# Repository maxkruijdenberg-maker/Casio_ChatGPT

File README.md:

# ChatGPT voor Casio — V40.1

Rustigere interface, modelinfo op F2 en een volledige verbindingscontrole. Na iedere bevestigde modelkeuze volgt automatisch één kleine betaalde API-test. Het actieve model wordt alleen bevestigd met passende API-modelmetadata.

[V40.1 downloaden](https://github.com/maxkruijdenberg-maker/Casio_ChatGPT/archive/refs/tags/download-v40.1-r1.zip) · [Handleiding](docs/V40.1-HANDLEIDING.md) · [Bijwerken](UPGRADE-V40.1.md) · [Alle downloads](DOWNLOADS.md)

Werk de Casio-app én je wifi-module bij. Er zijn aparte builds voor de ATOM-testbench en de ESP32-C6 Rev E-print. Behoud CGPT3; volledig wissen is niet nodig. Internet/account/modelcontrole gebruikt een echte kleine aanvraag en geeft geen exact tegoedsaldo. Zie de handleiding voor kosten en annuleren.

De builds en hosttests slagen; echte hardware/API-tests voor deze nieuwe versie moet je nog uitvoeren. De bestaande Rev E-productiebestanden blijven beschikbaar. Voor de nieuwe zelf te solderen XIAO-print gebruik je de aparte Rev G-bestanden hieronder.

## Actuele PCB: Rev G, drie Casio-draden

**Voor alleen Casio TX/RX/GND: gebruik Rev G. Rev F vereist een vierde VIO-draad en is daarvoor niet geschikt.**

[Download JLCPCB-set](https://github.com/maxkruijdenberg-maker/Casio_ChatGPT/archive/refs/tags/download-pcb-revg-r1.zip) · [Drie productie-bestanden](hardware/RevG-XIAO-3wire-06mm-OSP) · [Onderdeelcontrole](hardware/RevG-XIAO-ontwerp/ONDERDELENCONTROLE.md) · [Nieuwe XIAO-firmware + Casio-app](https://github.com/maxkruijdenberg-maker/Casio_ChatGPT/archive/refs/tags/download-xiao-revg-r1.zip)

Rev G: eigen XIAO zonder headerrails; 38 fabriekscomponenten / 20 codes; 89×34mm, 0,6mm, 2 lagen, OSP. Driepolige JST GH-uitgang; geen VIO-draad. TI-voedingsland/mask/stencil-patroon verwerkt; nieuwe uitgang met normale 3V3 UART-polariteit. Alleen de bijbehorende Rev G-firmware gebruiken. 26 hosttestgroepen en XIAO-build slagen; digitale controles schoon. Eerste PCBA nog fysiek te testen. [Handleiding en schema](hardware/RevG-XIAO-ontwerp/README.md).

## Installeren en bouwen

Open START-HIER.html uit het uitgepakte klantpakket. Arduino IDE 2, ESP32-core 3.3.0 en ArduinoJson 7.4.2 zijn gebruikt. De ATOM-sketch staat in atom/ChatGPTAtom, de C6-sketch in esp32c6/ChatGPTC6. Voor C6: ESP32C6 Dev Module, 4 MB, Huge APP, USB CDC uit. Laat alle headers bij de sketches staan.

ASAN_OPTIONS=detect_leaks=0 bash tools/test.sh draait de hosttests in de voorbereide omgeving. tools/sync_c6.py synchroniseert de gedeelde backend met behoud van de aparte C6-pinnen en zendsper.

[Schermvoorbeelden](docs/design/V40.1-actual-screens.png) · [Validatiestatus](docs/V40.1-CONTROLE-VOOR-VERKOOP.md) · [PCB-bestanden Rev E 0,6 mm/OSP](hardware/RevE-06mm-OSP)

Oudere versies blijven beschikbaar via de Git-tags en bestaande upgradegidsen.

V40.1: Info op F2; Model toont de bevestigde naam. De statusbadge verschijnt alleen op het chatbeginscherm. Eindtekens en onzichtbare opmaak worden beter weergegeven. Na 35 seconden zonder Casio-contact schakelt de wifi-radio uit en gaat de CPU naar 80 MHz; UART-contact herstelt de normale werking. Deze stroom- en herverbindingswerking is nog niet fysiek gemeten.

## Oudere PCB: Rev F, met vierde Casio-VIO-aansluiting

[Download JLCPCB-pakket](https://github.com/maxkruijdenberg-maker/Casio_ChatGPT/archive/refs/tags/download-pcb-revf-r1.zip) · [Alleen drie productie-bestanden](hardware/RevF-XIAO-06mm-OSP) · [Ontwerp, maatvoering en controles](hardware/RevF-XIAO-ontwerp/README.md) · [Download XIAO-firmware + Casio-app](xiao/ChatGPT-XIAO-RevF-installatie.zip)

89 × 34 mm L-vorm, 0,6 mm, 2 lagen, OSP. JLCPCB monteert 41 SMT-onderdelen; U5 blijft leeg voor jouw eigen Seeed XIAO ESP32-C6. Veertien soldeergaten, geen headerrails, USB-C binnen de getekende contour, J3/J4 aan het rechteruiteinde. Geen schakelaar: programmeer de XIAO eerst los. Voor eventueel later USB-onderhoud altijd J3 los vóór USB; USB los vóór J3 terugplaatsen.

Gebruik uitsluitend de **XIAO**-firmware voor Rev F: RX GPIO17, TX GPIO16. De Atom- en Rev E-builds hebben andere pinnen. [Arduino IDE-instellingen](xiao/README.md).

Digitale controles: DRC/ERC/parity schoon; boorgaten, Gerber-padcentra en BOM/CPL gecontroleerd; XIAO-build geslaagd. De echte 7mm-inbouwhoogte, voeding/wifi-pieken, RF en UART moeten op een eerste PCBA worden getest. Dit is nog geen fysiek gekwalificeerde verkoopserie.

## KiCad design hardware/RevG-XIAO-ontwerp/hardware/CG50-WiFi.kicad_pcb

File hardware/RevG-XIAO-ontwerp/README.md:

# Rev G — XIAO ESP32-C6, alleen TX / RX / GND

**Gebruik deze versie voor de drie-draads Casio-aansluiting. Rev F vereiste een vierde VIO-draad en past niet bij die wens. Meng geen Rev F-hardware of firmware met Rev G.**

[Onderdeelcontrole en ontwerpkeuzes](ONDERDELENCONTROLE.md)

De XIAO wordt door jou vóór montage los geprogrammeerd en daarna op 14 doorgemetalliseerde gaten gesoldeerd, zonder headerrails of sockets. De XIAO levert zelf MCU, wifi, USB-C, programmering en 3V3-regeling. Er zit geen tweede ESP32, CH340, losse USB-C-connector of extra acculader op deze carrier.

- 89 × 34mm L-vorm; 34 × 34mm kop, 55 × 19mm arm. Twee lagen, 0,6mm FR4, OSP.
- JLCPCB monteert **38 onderdelen**, verdeeld over **20 bestelcodes**. U5 blijft leeg voor de eigen XIAO ESP32-C6.
- J3 en J4 zitten aan het rechteruiteinde; de USB-C van de XIAO valt binnen de getekende contour.
- Alleen Casio TX, RX en GND. Geen Casio-VIO-draad. De aparte batterijvoeding blijft uiteraard via J3 lopen.
- Geen voedingsschakelaar. Programmeer vooraf los; voor eventueel later USB-onderhoud J3 eerst los, dan USB aansluiten. USB verwijderen vóór J3 terugplaatsen.

## Bestellen bij JLCPCB

Gebruik uitsluitend de drie bestanden in `hardware/RevG-XIAO-3wire-06mm-OSP` of pak het buitenste `CG50-WiFi-RevG-3wire-JLCPCB.zip` uit:

1. `GERBER-RevG-XIAO-3wire-06mm-OSP.zip`: upload voor fabricage.
2. `BOM-JLCPCB.csv`: onderdelenlijst voor assemblage.
3. `CPL-JLCPCB.csv`: plaatsingsbestand voor assemblage.

Kies 2 lagen, afgewerkte dikte 0,6mm, OSP en bovenkant SMT-assemblage. Geen VIPPO nodig. U5 mag NIET door JLC worden gemonteerd. De via's zijn 0,6mm diameter / 0,3mm boring, buiten SMT-pads. Laat productie-/transportstroken zo nodig door JLC toevoegen zonder de afgewerkte contour aan te passen.

Gerber, boringen en CPL gebruiken dezelfde oorsprong: linksonder, X naar rechts en Y omhoog. JST-centra zijn gecorrigeerd voor de footprint-oorsprong: J3 +0,45mm en J4 +0,425mm in lokale voorwaartse richting. Controleer de JLC-preview op de voorbeeldafbeelding: connectoropeningen naar rechts, U5 leeg. Fabrikantspecifieke JLC-modelrotaties zijn niet via jouw account ingezien. Pas geen componentvervanging toe zonder footprint/pinout te controleren.

## Kabels en aansluitingen

| Positie | Verbinding | Kabelbehuizing |
|---|---|---|
| J3.1 | Ruwe 4×AAA BAT+ | JST SH SHR-02V-S, 1mm |
| J3.2 | BAT- / GND | Zelfde 2-polige kabel |
| J4.1 | **Casio TX → PCB RX** | JST GH GHR-03V-S, 1,25mm |
| J4.2 | **Casio RX ← PCB TX** | Zelfde 3-polige kabel |
| J4.3 | Casio GND | Zelfde 3-polige kabel |

J4 is gewijzigd naar een beschikbare **driepolige JST GH**. De oude vierpolige SH-kabel past hier niet. J3 is SH, J4 is GH: verschillende stekkerfamilies. Controleer pinnummers en continuïteit; vertrouw niet op draadkleuren. Geschikte contacten/kabelassemblages apart aanschaffen. Voeg geen extra serieweerstanden toe: de carrier heeft die al.

## Montage en firmware

1. Programmeer de losse XIAO met `ChatGPT-XIAO-RevG-3wire-installatie.zip`. Arduino: ESP32-core 3.3.0, ArduinoJson 7.4.2, bord XIAO_ESP32C6, Huge APP, USB CDC Enabled. Alleen deze bordkeuze wordt geaccepteerd. De bestaande Casio V40.1-app is compatibel en zit ook in dit pakket.
2. USB los; controleer de PCBA eerst zonder XIAO met een stroombegrensde voeding. Meet ongeveer 4,98V tussen U5.14 en U5.13; controleer op kortsluiting/polariteit.
3. Soldeer de XIAO bovenop met losse passende pennen of rechte draadstukjes: 14 gaten, 1,05mm boring, 2,54mm steek, 15,24mm rijafstand. USB wijst naar de onderrand van de kop. Isoleer de onderkant van de XIAO en houd het antennegebied vrij. Sluit de onderste XIAO-BAT-pads nergens op aan.
4. Voed via J3, verbind de drie Casio-signalen via J4 en open ChatGPT. Firmware: RX GPIO17, **normale, niet-geïnverteerde TX GPIO16**; GPIO1 heartbeat, GPIO2 arm. De Rev F-firmware gebruikt andere uitgangspolariteit en is hiervoor ongeschikt.
5. Controleer op de echte eerste PCBA voeding, wifi, UART, opnieuw openen/sluiten en de totale inbouwhoogte inclusief isolatie/kabels voordat de behuizing definitief dichtgaat.

De uitgang is een 3V3-buffer zoals het signaaltype van de werkende ATOM-testbench, met hardware-zendsper. Alleen geldig Casio-protocolcontact kan de uitgang inschakelen. Na inschakelen krijgt de lijn 200us om hoog te worden voordat de eerste startbit wordt verzonden. Een lang laag blijvende RX-lijn zonder ontvangen data/protocolvoortgang sluit de uitgang vanaf 100ms; zonder geldig contact vervalt de lease na 30s. Wifi gaat na 35s contactverlies uit, CPU naar 80MHz. Dit is lijn-/protocolbewaking, geen rechtstreekse meting van de fysieke Casio-aan/uitstatus.

## Controles

DRC 0, ERC 0, onverbonden 0, schema/print-pariteit 0. Audit van bronnetten, alle componentposities, 14 XIAO-gaten, 53 via's, 174 koper-pad/via-centra en 67 boringen. Geen via in SMT-pads; geen XIAO in BOM/CPL/pasta. Voedingsberekening, TI-pinout en TI-land/mask/stencil-geometrie gecontroleerd; onderdelenmatches en catalogusvoorraad gecontroleerd. De nieuwe J4-code en bijbehorende fabrikantentabel zijn uit dezelfde vastgelegde catalogusrevisie gelezen.

De XIAO-build en 26 softwaretestgroepen slagen. Dit is een onderbouwd prototypeontwerp; voedingstransiënten, temperatuur, RF en de werkelijke Casio-ingang zijn nog niet op een gebouwde Rev G gemeten. Die resterende praktijktest is iets anders dan de nu uitgevoerde onderdeel- en ontwerplogicacontrole.

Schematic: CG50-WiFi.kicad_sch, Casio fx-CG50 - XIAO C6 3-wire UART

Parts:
C1, C4: 10uF 25V; C_0603_1608Metric; MPN TMK107BBJ106MA-T; LCSC C386081
C2, C3: 10uF 25V; C_0805_2012Metric; MPN CL21A106KAYNNNE; LCSC C15850
C5, C6, C7, C11, C12, C13: 22uF 16V; C_0805_2012Metric; MPN GRM21BC81C226ME44L; LCSC C258782
C8, C10, C15, C17: 100nF 50V; C_0603_1608Metric; MPN CC0603KRX7R9BB104; LCSC C14663
C9, C14: 1uF 50V; C_0603_1608Metric; MPN CL10A105KB8NNNC; LCSC C15849
J3: BAT JST SH 2P; JST_SH_SM02B-SRSS-TB_1x02-1MP_P1.00mm_Horizontal; MPN SM02B-SRSS-TB(LF)(SN); LCSC C160402
J4: CASIO TX RX GND / JST GH 3P; JST_GH_SM03B-GHS-TB_1x03-1MP_P1.25mm_Horizontal; MPN SM03B-GHS-TB(LF)(SN); LCSC C514175
L1: 1.5uH; L_Sunlord_SWPA4020S; MPN SWPA4020S1R5NT; LCSC C42099
Q1: AO3401A; SOT-23; MPN AO3401A; LCSC C15127
R1: 422k; R_0603_1608Metric; MPN 0603WAF4223T5E; LCSC C23169
R2, R5, R8, R10, R13, R14: 100k; R_0603_1608Metric; MPN 0603WAF1003T5E; LCSC C25803
R3: 10k; R_0603_1608Metric; MPN 0603WAF1002T5E; LCSC C25804
R4, R6: 1k; R_0603_1608Metric; MPN 0603WAF1001T5E; LCSC C21190
R7: 100R; R_0603_1608Metric; MPN 0603WAF1000T5E; LCSC C22775
R12, R15: 200k; R_0603_1608Metric; MPN 0603WAF2003T5E; LCSC C25811
R16: 38.3k; R_0603_1608Metric; MPN 0603WAF3832T5E; LCSC C23034
U1: TPS63070RNMR / 4.978V; RNM0015A; MPN TPS63070RNMR; LCSC C109322
U3: SN74LVC1G17DBVR; SOT-23-5; MPN SN74LVC1G17DBVR; LCSC C7836
U4: SN74LVC1G123DCTR; SSOP-8_2.95x2.8mm_P0.65mm; MPN SN74LVC1G123DCTR; LCSC C123302
U5: XIAO ESP32-C6 / HAND SOLDER, NO HEADERS; XIAO-C6-THT-14-Customer; MPN Seeed XIAO ESP32-C6 without headers
U6: SN74LVC1G126DBVR; SOT-23-5; MPN SN74LVC1G126DBVR; LCSC C7834

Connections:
/3V3: C10.1, C15.1, C17.1, R8.2, R12.1, U3.5 (VCC), U4.8 (VCC), U5.12 (3V3_OUT), U6.5 (VCC)
/BAT+: J3.1, Q1.3 (D)
/CASIO_RX: J4.2, R6.2
/CASIO_TX: J4.1, R4.1
/EN: R1.2, R2.1, U1.14 (EN)
/FB: R15.2, R16.1, U1.5 (FB)
/GND: C1.2, C2.2, C3.2, C4.2, C5.2, C6.2, C7.2, C8.2, C9.2, C10.2, C11.2, C12.2, C13.2, C15.2, C17.2, J3.2, J4.3, Q1.1 (G), R2.2, R5.2, R10.2, R13.2, R14.2, R16.2, U1.4 (GND), U1.10 (PGND), U1.15 (VSEL), U3.3 (GND), U4.1 (A), U4.4 (GND), U5.13 (GND), U6.3 (GND)
/HEARTBEAT: R14.1, U4.2 (B), U5.2 (D1_GPIO1)
/MONO_C: C14.2, U4.6 (CEXT)
/MONO_RC: C14.1, R12.2, U4.7 (REXT_CEXT)
/PS: R3.2, U1.1 (PS/SYNC)
/REG5V: C4.1, C5.1, C6.1, C7.1, C9.1, C11.1, C12.1, C13.1, R15.1, U1.7 (VOUT), U1.8 (VOUT), U5.14 (VBUS_5V)
/RX_IN: R4.2, R5.1, U3.2 (A)
/RX_WAKE: U3.4 (Y), U5.1 (D0_GPIO0), U5.8 (D7_GPIO17_RX)
/SW1: L1.1, U1.11 (L1)
/SW2: L1.2, U1.9 (L2)
/TX_ARM: R13.1, U4.3 (CLR_N), U5.3 (D2_GPIO2)
/TX_DATA: R7.2, R8.1, U6.2 (A)
/TX_ENABLE: R10.1, U4.5 (Q), U6.1 (OE)
/TX_GPIO: R7.1, U5.7 (D6_GPIO16_TX)
/TX_OUT: R6.1, U6.4 (Y)
/VAUX: C8.1, U1.3 (VAUX)
/VIN: C1.1, C2.1, C3.1, Q1.2 (S), R1.1, R3.1, U1.12 (VIN), U1.13 (VIN)

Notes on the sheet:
REV G | 89x34 L outline | 0.6mm | OSP | 2 copper layers
CUSTOMER installs XIAO ESP32-C6 without headers; 14 PTH holes only. Exclude U5 from PCBA.
USB-C belongs to XIAO; no factory-mounted bare C6, CH340C, USB connector or programmer.
TPS63070 adjustable: 200k / 38.3k -> 4.978V nominal; U5 provides 3V3 for the logic.
Disconnect J3 battery BEFORE connecting USB. Program XIAO before installation.
XIAO D7 GPIO17 RX, D6 GPIO16 normal TX; D1 GPIO1 heartbeat; D2 GPIO2 arm.
J3: 1 BAT+, 2 GND. J4: 1 Casio TX, 2 Casio RX, 3 GND, three wires only.
No vias in SMT lands; normal tented through vias. No VIPPO process requested.
Physical installed height <=7mm, USB envelope and power/RF behavior need first-article tests.

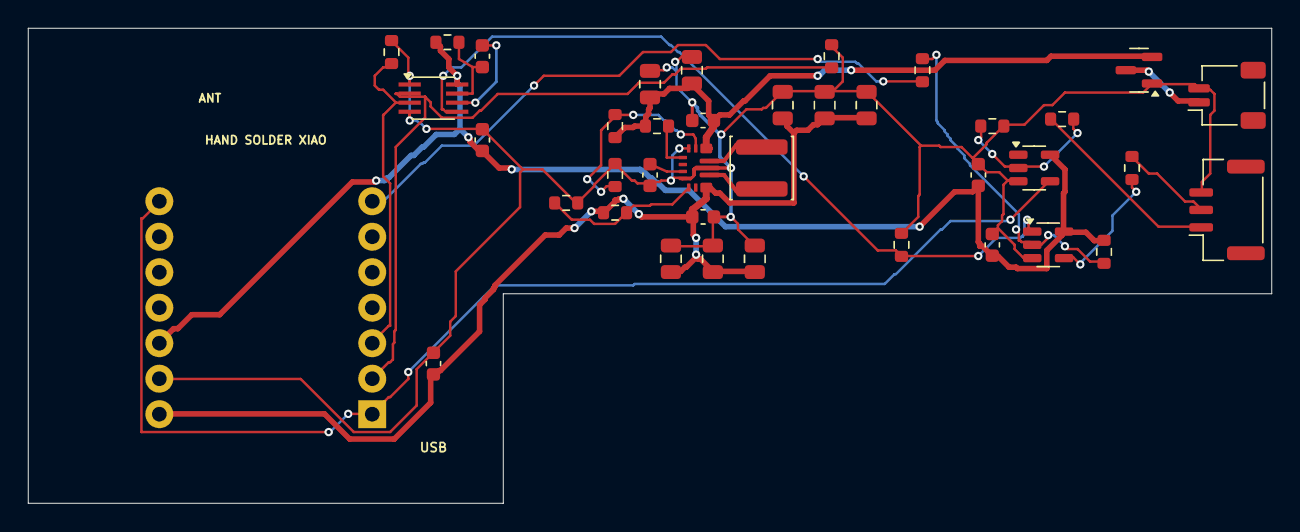
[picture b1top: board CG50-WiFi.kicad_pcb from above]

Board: 2 copper layers, 89.0 x 34.0 mm, 39 parts (0 on the bottom side), 23 nets.
